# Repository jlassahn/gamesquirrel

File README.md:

# gamesquirrel
A handheld game console.

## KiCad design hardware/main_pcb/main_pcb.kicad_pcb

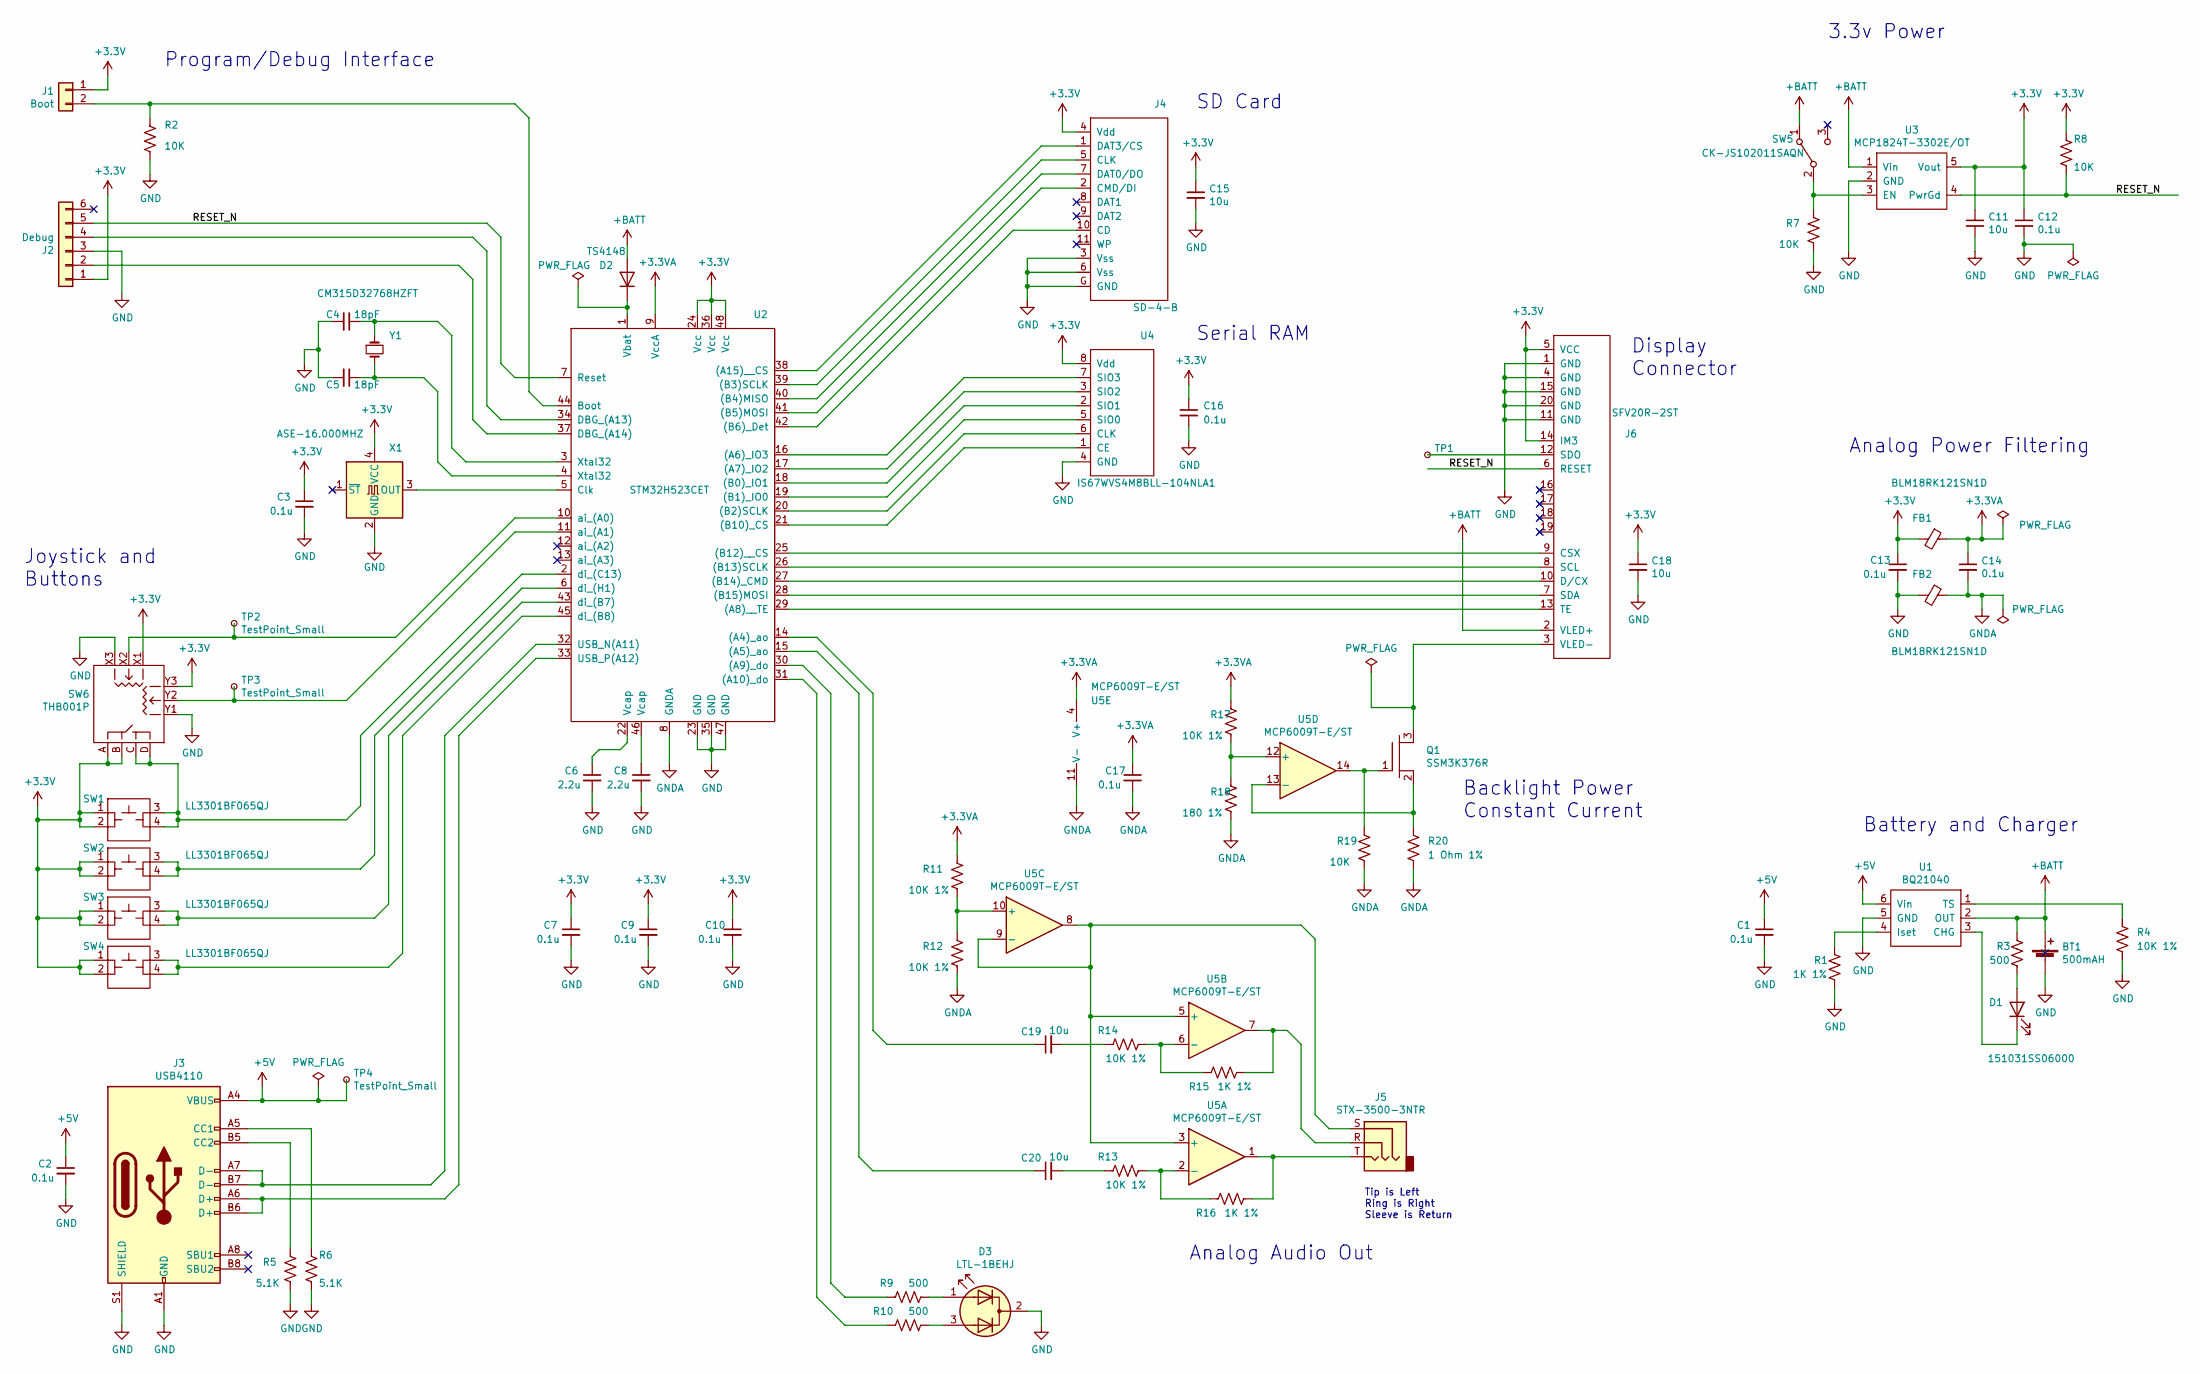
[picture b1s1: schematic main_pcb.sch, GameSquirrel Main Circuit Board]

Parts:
BT1: 500mAH; PinHeader_1x02_P1.27mm_Vertical
C1, C2, C3, C7, C9, C10, C12, C13, C14, C16, C17: 0.1u; C_0603_1608Metric
C4, C5: 18pF; C_0603_1608Metric
C6, C8: 2.2u; C_0603_1608Metric
C11, C15, C18, C19, C20: 10u; C_0805_2012Metric
D1: 151031SS06000; LED_D3.0mm
D2: TS4148; D_0603_1608Metric
D3: LTL-1BEHJ; LED_D3.0mm-3
FB1, FB2: BLM18RK121SN1D; R_0603_1608Metric
J1: Boot; PinSocket_1x02_P2.54mm_Vertical
J2: Debug; PinSocket_1x06_P2.54mm_Vertical
J3: USB4110
J4: SD-4-B
J5: STX-3500-3NTR; Jack_3.5mm_CUI_SJ-3523-SMT_Horizontal
J6: SFV20R-2ST; FPC_1x20_P0.5mm_top
Q1: SSM3K376R; SOT-23
R1, R15, R16: 1K 1%; R_0603_1608Metric
R2, R7, R8, R19: 10K; R_0603_1608Metric
R3, R9, R10: 500; R_0603_1608Metric
R4, R11, R12, R13, R14, R17: 10K 1%; R_0603_1608Metric
R5, R6: 5.1K; R_0603_1608Metric
R18: 180 1%; R_0603_1608Metric
R20: 1 Ohm 1%; R_0603_1608Metric
SW1, SW2, SW3, SW4: LL3301BF065QJ; LL3301-J
SW5: CK-JS102011SAQN; SW_SPDT_CK-JS102011SAQN
SW6: THB001P
TP1, TP2, TP3, TP4: TestPoint_Small; TestPoint_Pad_D1.5mm
U1: BQ21040; TSOT-23-6
U2: STM32H523CET; LQFP-48_7x7mm_P0.5mm
U3: MCP1824T-3302E/OT; TSOT-23-5
U4: IS67WVS4M8BLL-104NLA1; SOIC-8_3.9x4.9mm_P1.27mm
U5: MCP6009T-E/ST; TSSOP-14_4.4x5mm_P0.65mm
X1: ASE-16.000MHZ; Oscillator_SMD_Abracon_ASE-4Pin_3.2x2.5mm
Y1: CM315D32768HZFT; Crystal_SMD_3215-2Pin_3.2x1.5mm

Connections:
+3.3VA: C14.1, C17.1, FB1.1, R11.1, R17.1, U2.9 (VccA), U5.4 (V+)
+5V: C1.1, C2.1, J3.A4 (VBUS), J3.A9 (VBUS), J3.B4 (VBUS), J3.B9 (VBUS), TP4.1, U1.6 (Vin)
+BATT: BT1.1 (+), D2.2 (A), J6.2 (VLED+), R3.1, SW5.1 (A), U1.2 (OUT), U3.1 (Vin)
/RESET_N: J2.5, J6.6 (RESET), R8.2, U2.7 (Reset), U3.4 (PwrGd)
GNDA: C14.2, C17.2, FB2.1, R12.2, R18.2, R19.2, R20.2, U2.8 (GNDA), U5.11 (V-)
unnamed: C4.1, U2.3 (Xtal32), Y1.1
unnamed: C5.1, U2.4 (Xtal32), Y1.2
unnamed: C6.1, U2.22 (Vcap)
unnamed: C8.1, U2.46 (Vcap)
unnamed: C19.1, U2.14 ((A4)_ao)
unnamed: C19.2, R14.1
unnamed: C20.1, U2.15 ((A5)_ao)
unnamed: C20.2, R13.1
unnamed: D1.1 (K), U1.3 (CHG)
unnamed: D1.2 (A), R3.2
unnamed: D2.1 (K), U2.1 (Vbat)
unnamed: D3.1 (A1), R9.2
unnamed: D3.3 (A2), R10.2
unnamed: J1.2, R2.1, U2.44 (Boot)
unnamed: J2.2, U2.37 (DBG_(A14))
unnamed: J2.4, U2.34 (DBG_(A13))
unnamed: J3.A5 (CC1), R6.1
unnamed: J3.A6 (D+), J3.B6 (D+), U2.33 (USB_P(A12))
unnamed: J3.A7 (D-), J3.B7 (D-), U2.32 (USB_N(A11))
unnamed: J3.B5 (CC2), R5.1
unnamed: J4.1 (DAT3/CS), U2.38 ((A15)__CS)
unnamed: J4.2 (CMD/DI), U2.41 ((B5)MOSI)
unnamed: J4.5 (CLK), U2.39 ((B3)SCLK)
unnamed: J4.7 (DAT0/DO), U2.40 ((B4)MISO)
unnamed: J4.10 (CD), U2.42 ((B6)_Det)
unnamed: J5.R, R15.2, U5.7
unnamed: J5.S, U5.3 (+), U5.5 (+), U5.8, U5.9 (-)
unnamed: J5.T, R16.2, U5.1
unnamed: J6.3 (VLED-), Q1.3 (D)
unnamed: J6.7 (SDA), U2.28 ((B15)MOSI)
unnamed: J6.8 (SCL), U2.26 ((B13)SCLK)
unnamed: J6.9 (CSX), U2.25 ((B12)__CS)
unnamed: J6.10 (D/CX), U2.27 ((B14)_CMD)
unnamed: J6.12 (SDO), TP1.1
unnamed: J6.13 (TE), U2.29 ((A8)__TE)
unnamed: Q1.1 (G), R19.1, U5.14
unnamed: Q1.2 (S), R20.1, U5.13 (-)
unnamed: R1.1, U1.4 (Iset)
unnamed: R4.1, U1.1 (TS)
unnamed: R7.1, SW5.2 (B), U3.3 (EN)
unnamed: R9.1, U2.30 ((A9)_do)
unnamed: R10.1, U2.31 ((A10)_do)
unnamed: R11.2, R12.1, U5.10 (+)
unnamed: R13.2, R16.1, U5.2 (-)
unnamed: R14.2, R15.1, U5.6 (-)
unnamed: R17.2, R18.1, U5.12 (+)
unnamed: SW1.3, SW1.4, SW6.C, SW6.D, U2.2 (di_(C13))
unnamed: SW2.3, SW2.4, U2.6 (di_(H1))
unnamed: SW3.3, SW3.4, U2.43 (di_(B7))
unnamed: SW4.3, SW4.4, U2.45 (di_(B8))
unnamed: SW6.X2, TP2.1, U2.10 (ai_(A0))
unnamed: SW6.Y2, TP3.1, U2.11 (ai_(A1))
unnamed: U2.5 (Clk), X1.3 (OUT)
unnamed: U2.16 ((A6)_IO3), U4.7 (SIO3)
unnamed: U2.17 ((A7)_IO2), U4.3 (SIO2)
unnamed: U2.18 ((B0)_IO1), U4.2 (SIO1)
unnamed: U2.19 ((B1)_IO0), U4.5 (SIO0)
unnamed: U2.20 ((B2)SCLK), U4.6 (CLK)
unnamed: U2.21 ((B10)_CS), U4.1 (CE)

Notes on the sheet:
Tip is Left Ring is Right Sleeve is Return
Battery and Charger
Analog Power Filtering
3.3v Power
Analog Audio Out
Backlight Power Constant Current
SD Card
Serial RAM
Display Connector
Joystick and Buttons
Program/Debug Interface

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
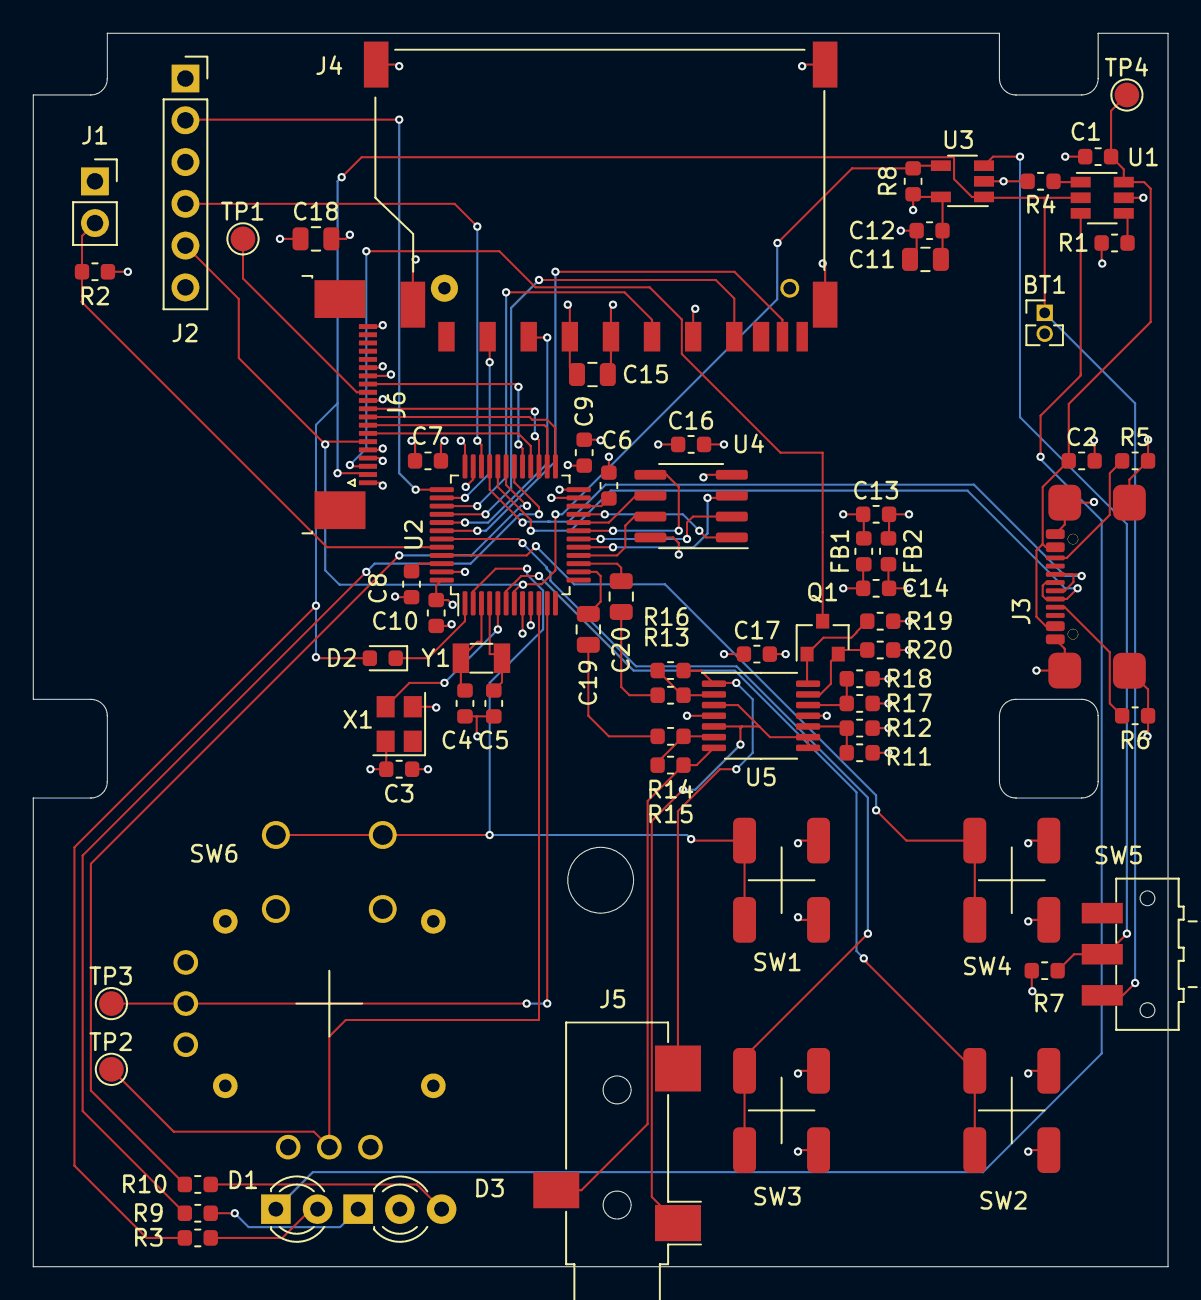
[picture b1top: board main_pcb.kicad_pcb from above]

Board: 4 copper layers, 69.0 x 75.0 mm, 70 parts (0 on the bottom side), 66 nets.

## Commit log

2025-01-25 Initial KiCAD circuit board design.
2025-02-22 License files, initial copy of generated STM32 configurations.
2025-03-15 Initial version of geometry OpenSCAD file.
2025-03-19 Remove build outputs from Git repo, add submodule for tinyusb.
2025-03-19 Some initial USB test code hacked from TinyUSB.
2025-03-19 Extern for CMSIS library.
2025-03-28 Move external/ directory to software/external.
2025-03-28 Makefile updates.
2025-04-05 Initialization experiments. Makefile improvements. USB descriptor changes.
2025-04-08 File system images for tests. prototype include files.
2025-04-21 Schematic cleanup, replace parts with latest selections, custom footprints for new parts.
2025-04-22 Layout for new PCB geometry.
2025-04-23 Joystick orientation, some trace cleanup, add text to PCB silkscreen.
2025-04-24 Reorganize makefiles.
2025-04-27 Minimal gamesquirrel main with UART.
2025-04-30 Prototype USB comm interface.
2025-05-03 Some USB code cleanup.
2025-05-03 USB comm Rx and Tx paths. Unit tests.
2025-05-03 USB interrupt handling.
2025-05-04 Redo GPIO setup.
2025-05-10 WIP removing HAL calls from setup.
2025-05-10 WIP remove more HAL calls from setup.
2025-05-11 First version that's working with the real PCB.
2025-05-12 Fix PLL settings, remove unneeded HAL files.
2025-05-13 More PLL and clock configuration, some rough notes in docs.
2025-05-14 More peripheral clock and enable setup. Configure a 1us system timer.
2025-05-18 More timer setup, buttons, variable brightness LEDs.
2025-05-25 Initial prototype of audio out with DMA, beginning of OctoSPI setup.
2025-05-26 Make OctoSPI work in memory mapped mode.
2025-06-07 Enable SPI interfaces for SD card and Display, enable ADC.
2025-06-08 Create linker scripts to match planned memory layout, add memory map table to doc.
2025-06-14 Reorganize bootstrap and interrupt vector table.
2025-06-14 Remove SystemInit call and system startup template file.
2025-06-15 Add sections for XDRAM and XSRAM data.
2025-06-15 Add editorconfig file and replace tabs with spaces.
2025-06-15 Add copyright to source files.
2025-06-17 Make SysTick a free-running timer, add clock delay function.
2025-06-22 Added disk read cache, beginning of FAT filesystem code.
2025-06-22 Fat filesystem root directory handling.
2025-06-22 FAT filesystem subdirectories and basic file reading.
2025-06-23 Basic SD card reads.
2025-06-24 FatFS on SD card.
2025-06-26 Fix analog input zero.
2025-07-09 Basic ELF file loader code.
2025-11-27 Some initialization cleanup. Make a basic display test work.

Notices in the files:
hardware/main_pcb/main_pcb.kicad_pcb:
SPDX-License-Identifier: CERN-OHL-P-2.0
Copyright 2025 Jeff Lassahn
License: CERN-OHL-P-2.0
